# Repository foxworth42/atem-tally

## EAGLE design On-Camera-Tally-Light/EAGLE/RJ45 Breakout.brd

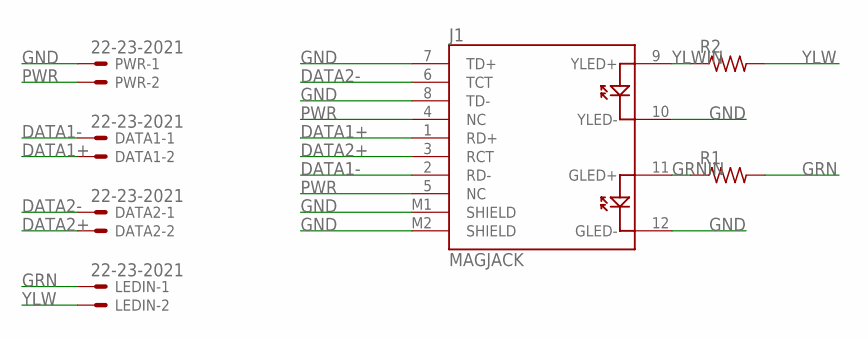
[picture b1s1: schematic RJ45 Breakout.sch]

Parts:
DATA1, DATA2: 22-23-2021
J1: MAGJACK
LEDIN: 22-23-2021
PWR: 22-23-2021
R1, R2: R-US_0207/10; 0207/10

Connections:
DATA1+: DATA1.2, J1.1 (RD+)
DATA1-: DATA1.1, J1.2 (RD-)
DATA2+: DATA2.2, J1.3 (RCT)
DATA2-: DATA2.1, J1.6 (TCT)
GND: J1.7 (TD+), J1.8 (TD-), J1.10 (YLED-), J1.12 (GLED-), J1.M1 (SHIELD), J1.M2 (SHIELD), PWR.1
GRN: LEDIN.1, R1.2
GRNIN: J1.11 (GLED+), R1.1
PWR: J1.4 (NC), J1.5 (NC), PWR.2
YLW: LEDIN.2, R2.2
YLWIN: J1.9 (YLED+), R2.1

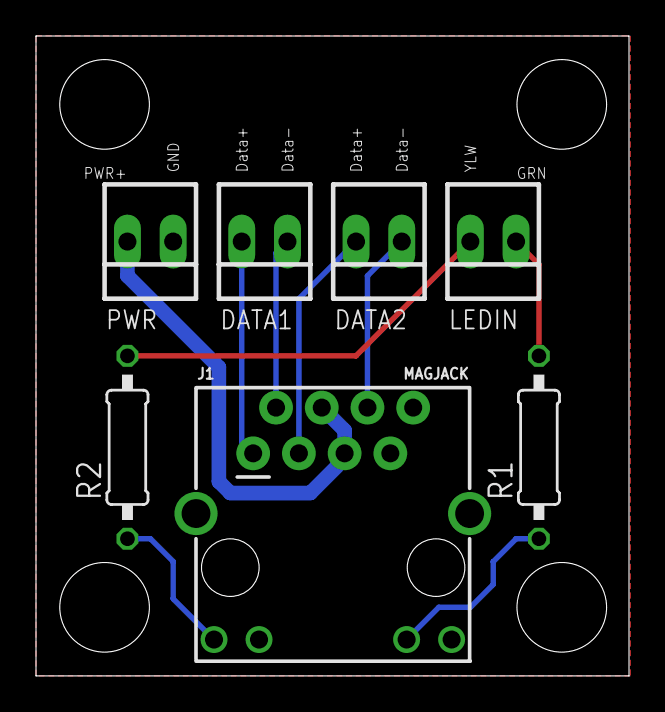
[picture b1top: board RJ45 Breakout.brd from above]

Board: 2 copper layers, 32.9 x 35.5 mm, 7 parts (0 on the bottom side), 10 nets.

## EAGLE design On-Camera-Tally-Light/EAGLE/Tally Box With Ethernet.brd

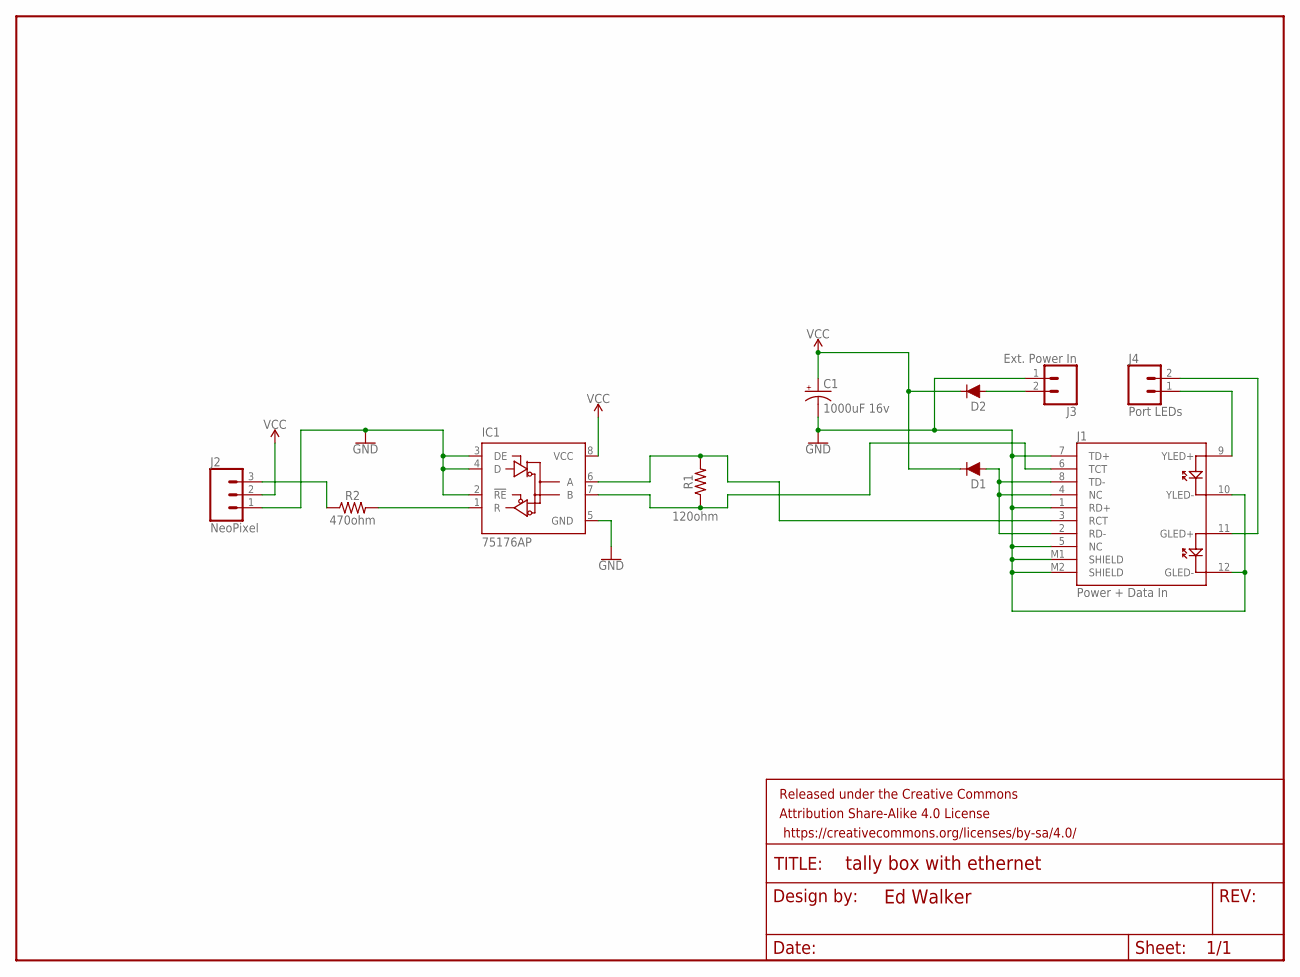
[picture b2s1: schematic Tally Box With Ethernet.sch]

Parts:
C1: 1000uF 16v; CPOL-RADIAL-5MM-10MM
D1, D2: DIODE-PTH; DIODE-1N4001
FRAME1: FRAME-LETTERNO_PACKAGE; DUMMY
IC1: 75176AP; DIL08
J1: Power + Data In; MAGJACK
J2: NeoPixel; 1X03
J3: Ext. Power In; 1X02
J4: Port LEDs; 1X02
R1: 120ohm; AXIAL-0.3
R2: 470ohm; AXIAL-0.3

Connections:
DATA: J2.3, R2.P$1 (1)
DATA+: IC1.6 (A), J1.3 (RCT), R1.P$2 (2)
DATA-: IC1.7 (B), J1.6 (TCT), R1.P$1 (1)
DATAOUT: IC1.1 (R), R2.P$2 (2)
GND: C1.-, IC1.2 (!RE), IC1.3 (DE), IC1.4 (D), IC1.5 (GND), J1.1 (RD+), J1.5 (NC), J1.7 (TD+), J1.10 (YLED-), J1.12 (GLED-), J1.M1 (SHIELD), J1.M2 (SHIELD), J2.1, J3.1
unnamed: J1.9 (YLED+), J4.1
unnamed: J1.11 (GLED+), J4.2
VCC: C1.+, D1.C, D2.C, IC1.8 (VCC), J2.2
VIN1: D1.A, J1.2 (RD-), J1.4 (NC), J1.8 (TD-)
VIN2: D2.A, J3.2

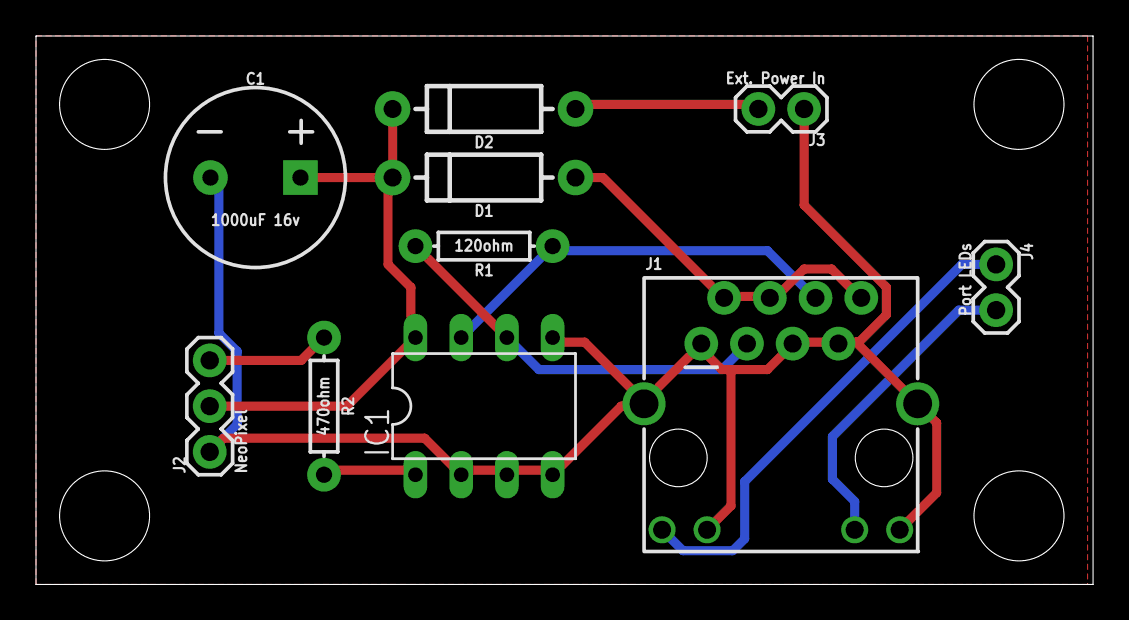
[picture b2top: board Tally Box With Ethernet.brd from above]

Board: 2 copper layers, 58.7 x 30.5 mm, 11 parts (0 on the bottom side), 10 nets.

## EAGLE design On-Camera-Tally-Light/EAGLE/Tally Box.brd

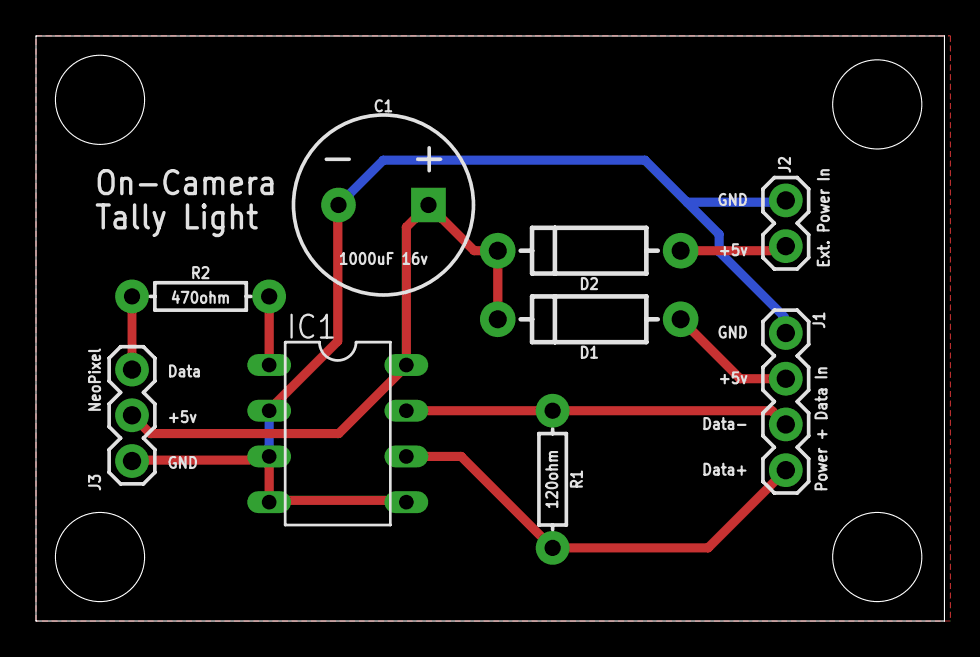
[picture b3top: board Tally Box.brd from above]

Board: 2 copper layers, 50.5 x 32.5 mm, 9 parts (0 on the bottom side), 8 nets.

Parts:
C1: 1000uF 16v; CPOL-RADIAL-5MM-10MM
D1, D2: DIODE-1N4001
IC1: 75176AP; DIL08
J1: Power + Data In; 1X04
J2: Ext. Power In; 1X02
J3: NeoPixel; 1X03
R1: 120ohm; AXIAL-0.3
R2: 470ohm; AXIAL-0.3

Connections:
DATA: J3.3, R2.P$1
DATA+: IC1.6, J1.4, R1.P$2
DATA-: IC1.7, J1.3, R1.P$1
DATAOUT: IC1.1, R2.P$2
GND: C1.-, IC1.2, IC1.3, IC1.4, IC1.5, J1.1, J2.1, J3.1
VCC: C1.+, D1.C, D2.C, IC1.8, J3.2
VIN1: D1.A, J1.2
VIN2: D2.A, J2.2

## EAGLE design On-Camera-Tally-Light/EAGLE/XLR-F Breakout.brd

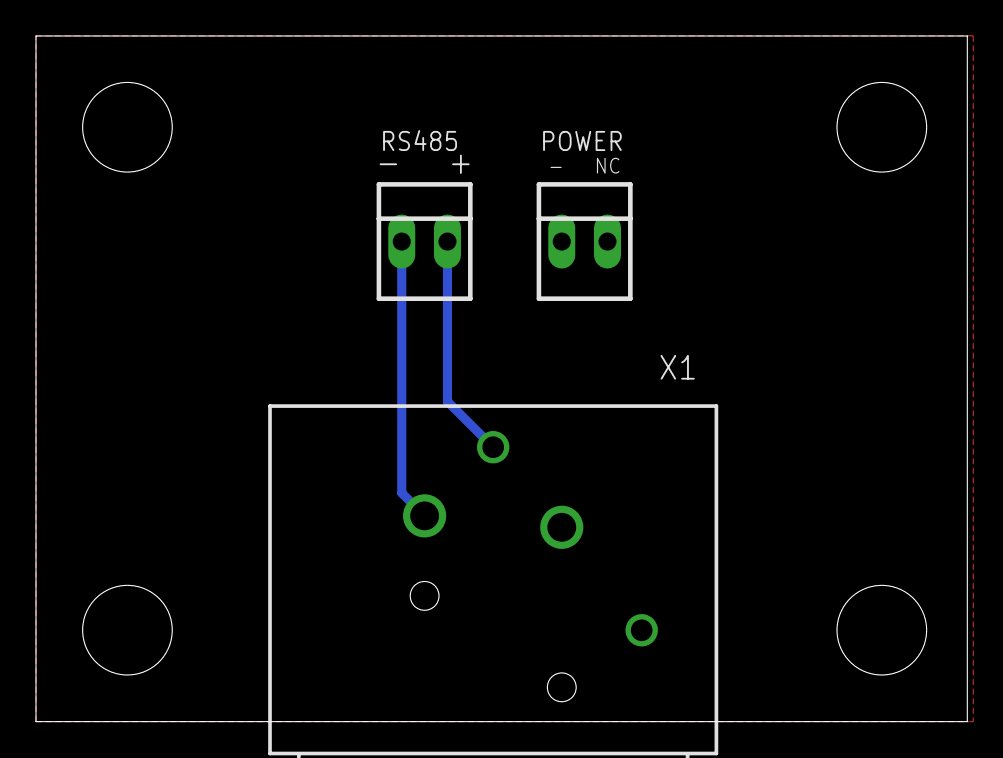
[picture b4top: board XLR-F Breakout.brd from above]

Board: 2 copper layers, 51.7 x 38.1 mm, 3 parts (0 on the bottom side), 3 nets.

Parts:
POWER: 22-23-2021
RS485: 22-23-2021
X1: NC3FAH2

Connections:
DATA+: RS485.2, X1.3
DATA-: RS485.1, X1.2
GND: POWER.1, X1.1, X1.G

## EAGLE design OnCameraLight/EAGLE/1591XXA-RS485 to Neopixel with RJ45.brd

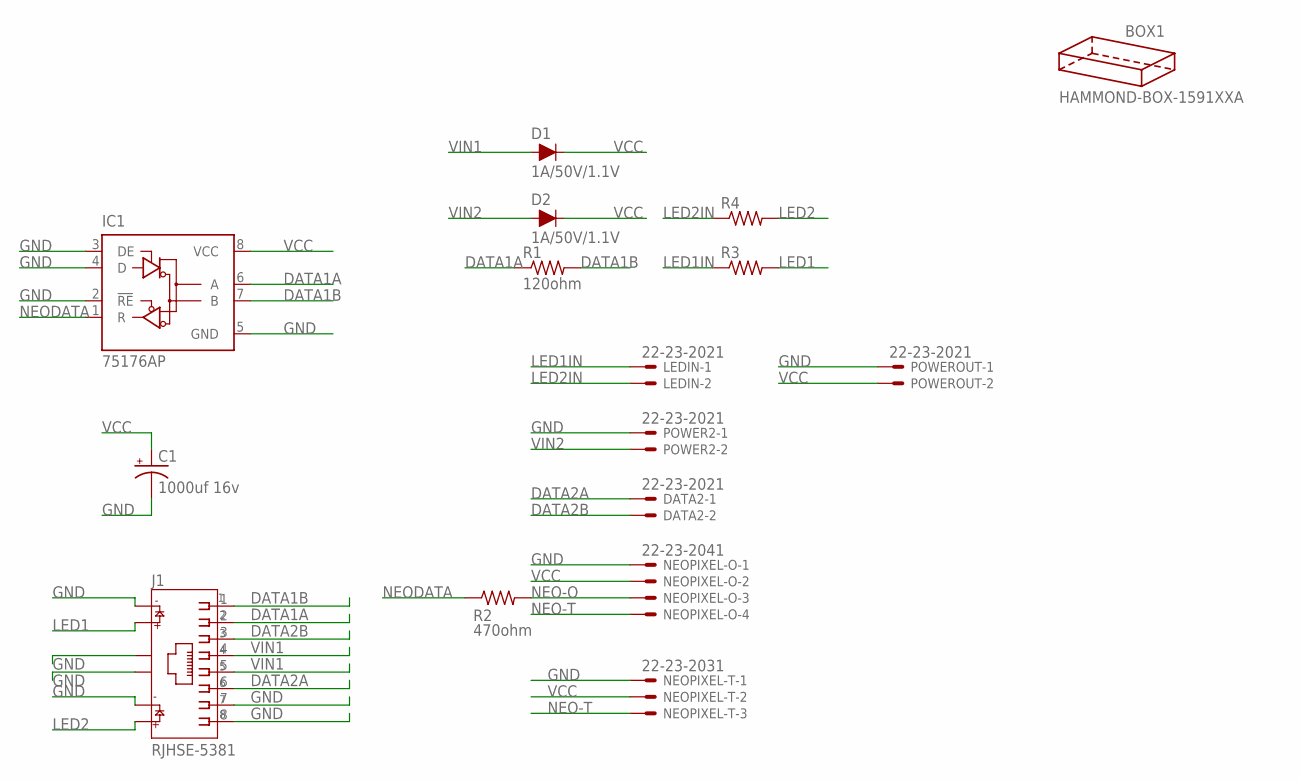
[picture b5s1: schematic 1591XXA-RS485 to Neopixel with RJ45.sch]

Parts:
BOX1: HAMMOND-BOX-1591XXA; 1591XXA
C1: 1000uf 16v; CPOL-RADIAL-5MM-10MM
D1, D2: 1A/50V/1.1V; DIODE-1N4001
DATA2: 22-23-2021
IC1: 75176AP; DIL08
J1: RJHSE-5381; AMPHENOL_RJHSE-5381
LEDIN: 22-23-2021
NEOPIXEL-O: 22-23-2041
NEOPIXEL-T: 22-23-2031
POWER2: 22-23-2021
POWEROUT: 22-23-2021
R1: 120ohm; 0207/10
R2: 470ohm; 0207/10
R3, R4: R-US_0207/10; 0207/10

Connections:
DATA1A: IC1.6 (A), J1.2, R1.1
DATA1B: IC1.7 (B), J1.1, R1.2
DATA2A: DATA2.1, J1.6
DATA2B: DATA2.2, J1.3
GND: C1.-, IC1.2 (!RE), IC1.3 (DE), IC1.4 (D), IC1.5 (GND), J1.7, J1.8, J1.9, J1.11, J1.S1, J1.S2, NEOPIXEL-O.1, NEOPIXEL-T.1, POWER2.1, POWEROUT.1
LED1: J1.10, R3.2
LED1IN: LEDIN.1, R3.1
LED2: J1.12, R4.2
LED2IN: LEDIN.2, R4.1
NEO-O: NEOPIXEL-O.3, R2.2
NEO-T: NEOPIXEL-O.4, NEOPIXEL-T.3
NEODATA: IC1.1 (R), R2.1
VCC: C1.+, D1.C, D2.C, IC1.8 (VCC), NEOPIXEL-O.2, NEOPIXEL-T.2, POWEROUT.2
VIN1: D1.A, J1.4, J1.5
VIN2: D2.A, POWER2.2

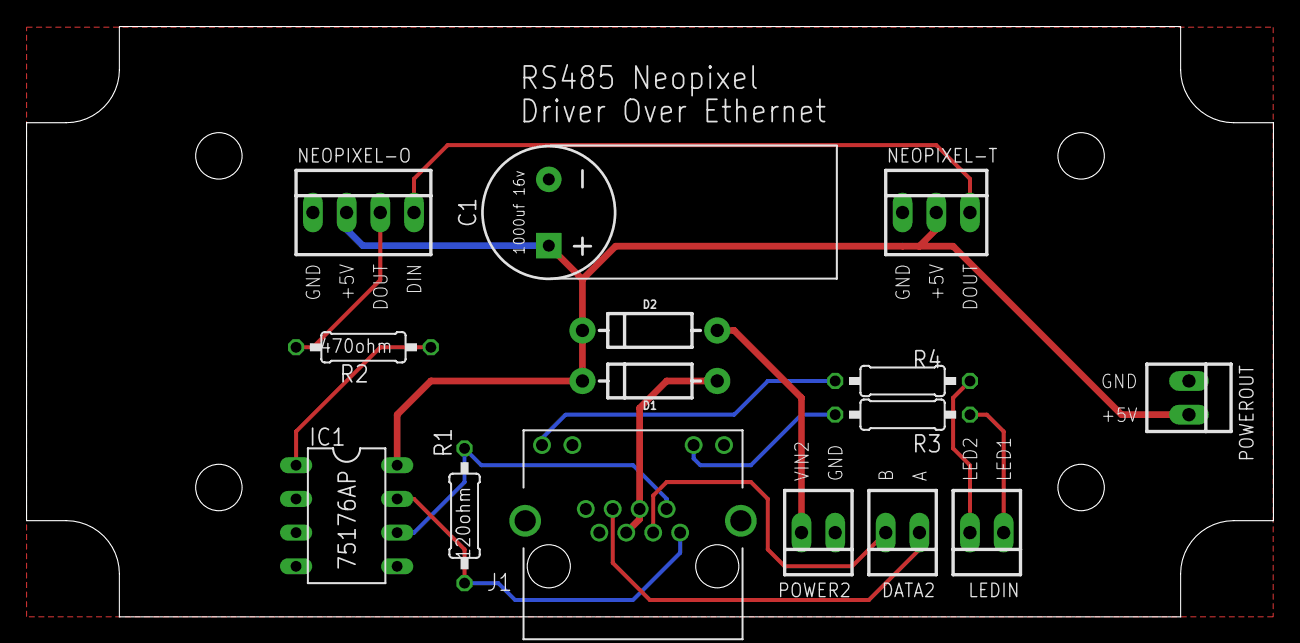
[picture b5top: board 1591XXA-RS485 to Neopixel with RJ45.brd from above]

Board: 2 copper layers, 94.0 x 44.5 mm, 16 parts (0 on the bottom side), 15 nets.

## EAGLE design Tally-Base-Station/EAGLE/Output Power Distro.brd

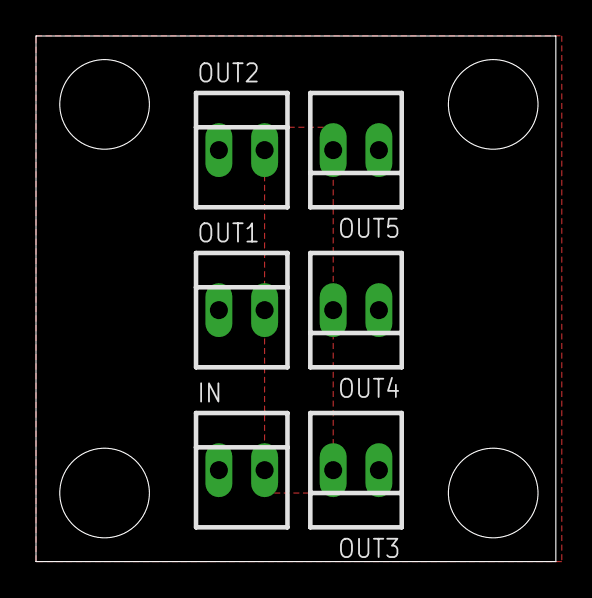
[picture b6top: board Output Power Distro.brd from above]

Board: 2 copper layers, 28.9 x 29.2 mm, 6 parts (0 on the bottom side), 2 nets, no tracks yet.

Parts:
IN: 22-23-2021
OUT1, OUT2, OUT3, OUT4, OUT5: 22-23-2021

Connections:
GND: IN.1, OUT1.1, OUT2.1, OUT3.1, OUT4.1, OUT5.1
VCC: IN.2, OUT1.2, OUT2.2, OUT3.2, OUT4.2, OUT5.2

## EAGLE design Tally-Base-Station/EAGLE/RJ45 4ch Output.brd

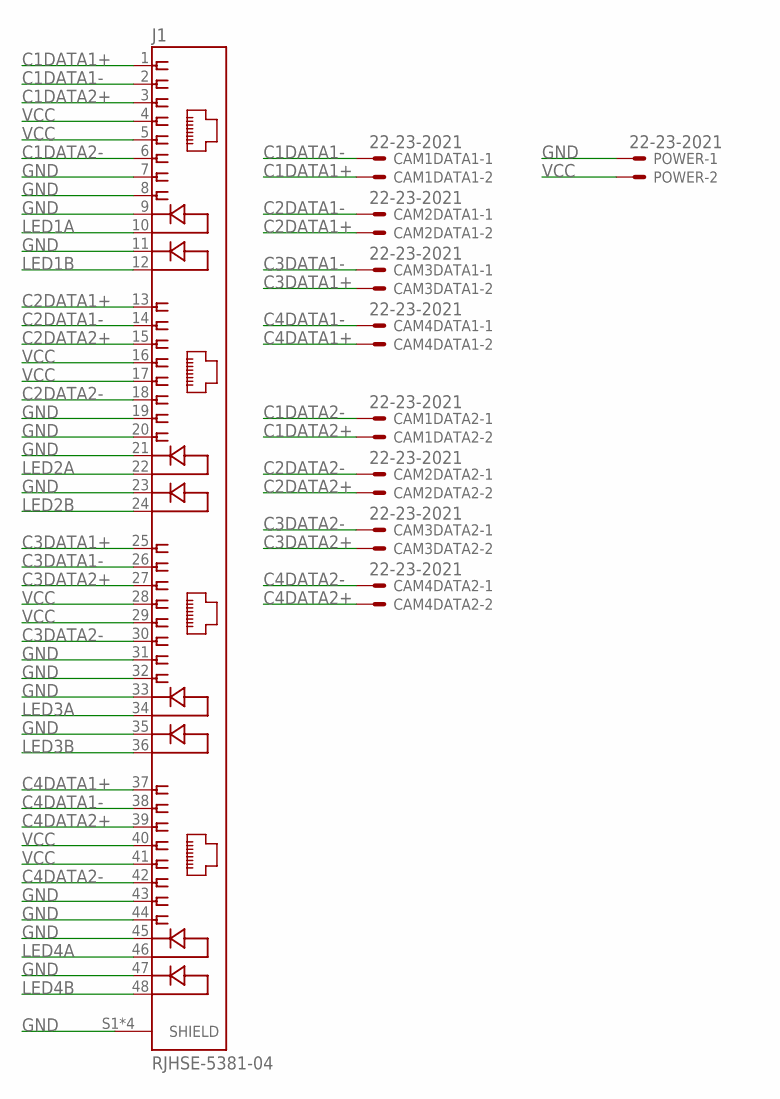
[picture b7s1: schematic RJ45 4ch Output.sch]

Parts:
CAM1DATA1, CAM1DATA2, CAM2DATA1, CAM2DATA2, CAM3DATA1, CAM3DATA2, CAM4DATA1, CAM4DATA2: 22-23-2021
J1: RJHSE-5381-04; AMPHENOL_RJHSE-5381-04
POWER: 22-23-2021

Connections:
C1DATA1+: CAM1DATA1.2, J1.1
C1DATA1-: CAM1DATA1.1, J1.2
C1DATA2+: CAM1DATA2.2, J1.3
C1DATA2-: CAM1DATA2.1, J1.6
C2DATA1+: CAM2DATA1.2, J1.13
C2DATA1-: CAM2DATA1.1, J1.14
C2DATA2+: CAM2DATA2.2, J1.15
C2DATA2-: CAM2DATA2.1, J1.18
C3DATA1+: CAM3DATA1.2, J1.25
C3DATA1-: CAM3DATA1.1, J1.26
C3DATA2+: CAM3DATA2.2, J1.27
C3DATA2-: CAM3DATA2.1, J1.30
C4DATA1+: CAM4DATA1.2, J1.37
C4DATA1-: CAM4DATA1.1, J1.38
C4DATA2+: CAM4DATA2.2, J1.39
C4DATA2-: CAM4DATA2.1, J1.42
GND: J1.7, J1.8, J1.9, J1.11, J1.19, J1.20, J1.21, J1.23, J1.31, J1.32, J1.33, J1.35, J1.43, J1.44, J1.45, J1.47, J1.S1 (SHIELD), J1.S2 (SHIELD), J1.S3 (SHIELD), J1.S4 (SHIELD), POWER.1
LED1A: J1.10
LED1B: J1.12
LED2A: J1.22
LED2B: J1.24
LED3A: J1.34
LED3B: J1.36
LED4A: J1.46
LED4B: J1.48
VCC: J1.4, J1.5, J1.16, J1.17, J1.28, J1.29, J1.40, J1.41, POWER.2

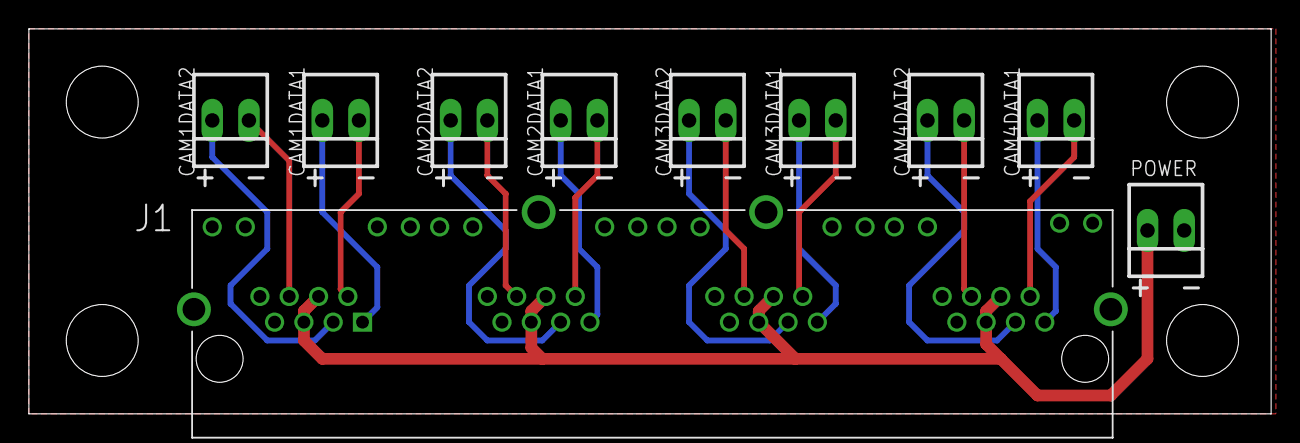
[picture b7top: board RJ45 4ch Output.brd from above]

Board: 2 copper layers, 86.0 x 26.7 mm, 10 parts (0 on the bottom side), 18 nets.

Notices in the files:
parts and their libraries:
SparkFun-Connectors: Licensing: Creative Commons ShareAlike 4.0 International - https://creativecommons.org/licenses/by-sa/4.0
SparkFun-Aesthetics: Released under the Creative Commons Attribution Share-Alike 4.0 License
SparkFun-Aesthetics: https://creativecommons.org/licenses/by-sa/4.0
